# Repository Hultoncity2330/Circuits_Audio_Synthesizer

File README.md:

# Audio Synthesizer — Logic Noise, Breadboard Prototypes & KiCad PCB

**Circuits / CreaTech A4 — November 2026**  
**Team:** Ryan Hulton, Paul Lamour

> An experimental audio synthesizer built from digital logic: we explored oscillator circuits on breadboards, documented their waveforms and sounds, modeled a circuit in Tinkercad, and developed an expanded KiCad schematic and PCB layout.

## 1. Concept and learning objectives

This project explores **logic noise**: producing audible signals from inexpensive digital logic rather than using a conventional synthesizer IC or generating all the audio in software. An inverting Schmitt trigger such as the **74HC14** can form a relaxation oscillator when its output is fed back through a resistance and its input is connected to a capacitor. Changing the resistance changes the charge/discharge timing, and therefore the oscillator frequency.

We experimented with several ways to shape and combine these oscillations. The **LM386** provides an audio amplification stage, while a **74HC595** shift register can drive an eight-LED visual output or support a later stepped control/sequencer design. The **Arduino Uno** shown in the Tinkercad setup is used in the prototyping environment; the KiCad PCB should be understood as a separate hardware design, not proof that an Arduino has been mounted on it.

**Main components represented across the experiments and CAD work:**

- **74HC14** — six inverters with Schmitt-trigger inputs, used for RC oscillator stages.
- **Variable resistors / potentiometers** — frequency adjustment.
- **Capacitors and fixed resistors** — timing, mixing, coupling and supporting circuits.
- **LM386** — audio amplifier for a small speaker.
- **74HC595** — 8-bit shift register and LED outputs.
- **LEDs and resistors** — visual indication, including current limiting in the PCB design.

The following is a **documentation of experiments and design work**; it does not claim that the finalized PCB has already been manufactured or physically tested.

## 2. Experimental process and audiovisual documentation

### 2.1 Breadboard experiments — 9 November 2026

These video files contain **video and embedded audio tracks**, so they are the primary audiovisual records of the breadboard sessions. Click each one to watch and listen on GitHub.

| Recording | Preview / focus | Duration |
| --- | --- | ---: |
| [12:20 — Early circuit test](media/20261109_122047.mp4) | Breadboard wiring, hands-on adjustment and a small speaker | ~7 s |
| [14:56 — Hands-on adjustment](media/20261109_145655.mp4) | Adjusting the breadboard circuit during experimentation | ~17 s |
| [15:11 — Oscilloscope measurement](media/20261109_151122.mp4) | Oscilloscope trace while the circuit is connected | ~37 s |
| [17:20 — Illuminated circuit](media/20261109_172049.mp4) | Breadboard prototype with an illuminated green LED | ~19 s |
| [10 November, 15:21 — Extended prototype](media/20261110_152147.mp4) | Multiple breadboards, Arduino, LED indicators and speaker | ~14 s |

*The descriptions above identify what is visible in the recordings. Precise pitch values, measurements and proof of a soldered assembly have not been independently established from the files.*

### 2.2 Breadboard photographs — 10 November 2026

**Prototype and stripboard preparation**

*Figure 1 — Breadboard setup, connected speaker, and a perforated prototyping board. The photo alone does not establish that the circuit is soldered and functional.*

**Expanded experimental setup**

*Figure 2 — More developed breadboard assembly with additional controls, an Arduino board, a speaker and a perforated board.*

### 2.3 Oscilloscope observations

The oscilloscope was used to inspect the changing electrical signals generated by the breadboard circuits. The screenshots show repeating traces; they should not be treated as calibrated measurements without the matching scale/cursor readings.

| Observation 1 | Observation 2 | Observation 3 |
| :---: | :---: | :---: |
|  |  |  |
| [Full image](media/oscilloscope1.png) | [Full image](media/oscilloscope2.png) | [Full image](media/oscilloscope3.png) |

These observations helped us compare the qualitative shapes of the signals while changing the circuit. For a quantitative account, add the actual oscilloscope time/division, voltage/division, probe attenuation and measured frequencies.

### 2.4 Hand-drawn circuit diagram

*Figure 3 — Working circuit sketch: oscillator/mixing concept, LM386 output stage and planned 74HC595 section. This is an experimental sketch, not the final PCB manufacturing drawing.*

## 3. Tinkercad — virtual breadboard and generated schematic

The experiment was also reconstructed in **Tinkercad Circuits** to show its component placement and wiring before the KiCad design stage.

### Virtual breadboard

[Open full-resolution breadboard image](tinkercad/Tinkercad_breadboard.png)

### Generated electronic schematic

**[View the Tinkercad-generated schematic (PDF)](tinkercad/Tinkercad_schematic.pdf)**

The Tinkercad schematic and physical breadboard view are useful references, but the later KiCad schematic was reconstructed separately, with some implementation changes and design checks. In particular, the real **LM386** pinout must be used for the audio stage rather than treating an incorrectly named amplifier in Tinkercad as electrically interchangeable.

> **File-path check:** These two Tinkercad links use the names seen in the project folder (`Tinkercad_breadboard.png` and `Tinkercad_schematic.pdf`). If the GitHub filenames differ, update these two links to match their exact spelling/capitalization.

## 4. KiCad — expanded schematic and PCB design

The KiCad deliverable is stored in:

**[`kicad/Circuits_Audio_Synth_Kicad_VF/`](kicad/Circuits_Audio_Synth_Kicad_VF/)**

| File | Purpose |
| --- | --- |
| [`Circuits_Audio_Synth_Kicad_VF.kicad_pro`](kicad/Circuits_Audio_Synth_Kicad_VF/Circuits_Audio_Synth_Kicad_VF.kicad_pro) | KiCad project settings |
| [`Circuits_Audio_Synth_Kicad_VF.kicad_sch`](kicad/Circuits_Audio_Synth_Kicad_VF/Circuits_Audio_Synth_Kicad_VF.kicad_sch) | Editable schematic |
| [`Circuits_Audio_Synth_Kicad_VF.kicad_pcb`](kicad/Circuits_Audio_Synth_Kicad_VF/Circuits_Audio_Synth_Kicad_VF.kicad_pcb) | PCB component layout and copper routing |
| [`AudioSynth_Local.pretty/`](kicad/Circuits_Audio_Synth_Kicad_VF/AudioSynth_Local.pretty/) | Project-specific footprints |
| [`Custom.kicad_sym`](kicad/Circuits_Audio_Synth_Kicad_VF/Custom.kicad_sym) | Project-specific schematic symbol library |
| `fp-lib-table` and `sym-lib-table` | Local library registrations |

### Second-version concept / added functionality

Compared with the initial oscillator/mixing experiment, the expanded KiCad design brings together **five adjustable oscillator sections**, **LM386 audio output circuitry**, and an **eight-output 74HC595/LED subsystem** on one PCB design. This provides more possible oscillator combinations and visual output/step-sequencer development than the simple initial oscillator setup.

The eight-LED shift-register section is a **design feature**, not evidence that a complete clocked musical sequencer has been demonstrated on a finished PCB. If the assessment requires an implemented novel behavior, the team should document its actual operation and what was added relative to the **soldered** V1 circuit.

### Layout and verification

- Components are arranged in functional groups: oscillator/timing networks, logic and amplifier ICs, and LED outputs.
- The PCB uses routed front/back copper and a ground copper zone.
- The **last KiCad DRC screenshot provided for the final v8** reported **0 errors**, **0 warnings**, **0 unconnected items**, and **0 schematic/PCB parity discrepancies** (with **5 ignored tests**).
- **These results are CAD rule checks, not a functional test or an assurance of manufacturability.** Actual component-body dimensions and custom footprint geometries must be compared with the parts that will be soldered.

To edit the design, open the `.kicad_pro` file from the directory above and keep the local symbol and footprint libraries in their existing relative positions.

## 5. Soldered prototype

### 5.1 Assembly and soldering progress

After testing our audio synthesizer circuits on breadboards, we began transferring the components onto perforated prototyping boards to build a more permanent physical prototype.

**The soldering process has not yet been completed successfully.** We encountered difficulties assembling the boards and making reliable electrical connections between the components. The photograph below shows the current assembly progress, including the boards for the LED outputs, electronic components and adjustable controls.

*Figure 4 — Work-in-progress assembly on perforated prototyping boards. The soldering and interconnections have not yet been finalized.*

### 5.2 Current status and next steps

Although we tested various oscillator circuits during the breadboard experiments, **we cannot yet confirm that the soldered assembly works**. No functioning soldered prototype has been demonstrated at the time of submission.

Our next steps are to complete the solder joints and wiring, check continuity and possible short circuits, verify the power connections, and test the assembled synthesizer before recording evidence of its operation.

This section documents the unfinished state of the physical prototype rather than presenting it as a completed or verified circuit.

## 6. What we learned and possible next steps

- Simple Schmitt-trigger logic can be used as an experimental sound source with RC feedback.
- Potentiometers change oscillator timing and can create a wide range of audible behavior.
- An oscilloscope is useful for comparing waveforms and investigating unexpected behavior.
- Moving from breadboard experiments to Tinkercad and KiCad requires careful attention to physical pinouts, power rails, resistor values, PCB footprints and track clearances.
- A successful ERC/DRC is necessary for CAD verification, but does **not** guarantee the actual circuit will work after assembly.

Possible future work includes demonstrating a fully clocked 74HC595-driven step pattern, measuring oscillator frequencies quantitatively, testing the soldered hardware and producing a fabrication-verified revision with confirmed component footprints.

## 7. Repository organization

```text
Circuits_Audio_Synthesizer/
├── README.md
├── kicad/
│   └── Circuits_Audio_Synth_Kicad_VF/
│       ├── Circuits_Audio_Synth_Kicad_VF.kicad_pro
│       ├── Circuits_Audio_Synth_Kicad_VF.kicad_sch
│       ├── Circuits_Audio_Synth_Kicad_VF.kicad_pcb
│       ├── AudioSynth_Local.pretty/
│       ├── Custom.kicad_sym
│       ├── sym-lib-table
│       └── fp-lib-table
├── tinkercad/
│   ├── Tinkercad_breadboard.png
│   └── Tinkercad_schematic.pdf
└── media/
    ├── 20261109_122047.mp4
    ├── 20261109_145655.mp4
    ├── 20261109_151122.mp4
    ├── 20261109_172049.mp4
    ├── 20261110_102235.jpg
    ├── 20261110_143109.jpg
    ├── 20261110_152147.mp4
    ├── hand_drawn_circuit.jpg
    ├── oscilloscope1.png
    ├── oscilloscope2.png
    └── oscilloscope3.png
```

---

**Course context:** Logic Noise / Digital Oscillators workshop, CreaTech Circuits, November 2026.  
**Repository:** https://github.com/Hultoncity2330/Circuits_Audio_Synthesizer

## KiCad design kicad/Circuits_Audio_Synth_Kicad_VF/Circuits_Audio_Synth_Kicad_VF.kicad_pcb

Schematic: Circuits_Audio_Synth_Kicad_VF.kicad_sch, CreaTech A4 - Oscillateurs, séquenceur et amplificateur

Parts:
C1, C2, C3, C4, C5, C6: 2.2uF; C_Disc_D5.0mm_W2.5mm_P5.00mm
C7: 2.2uF; CP_Radial_D6.3mm_P2.50mm
C8: 220uF; CP_Radial_D6.3mm_P2.50mm
C11, C12, C13: 100nF; C_Disc_D5.0mm_W2.5mm_P5.00mm
D1, D2, D3, D4, D5, D6, D7, D8, D12: GREEN; LED_D5.0mm
D10: RED; LED_D5.0mm
D11: YELLOW; LED_D5.0mm
D13: BLUE; LED_D5.0mm
J1: ARDUINO_5V_GND; PinHeader_1x02_P2.54mm_Vertical
LS1: Speaker_8ohm; PinHeader_1x02_P2.54mm_Vertical
R1, R2, R3, R4, R5, R11, R12, R13, R14, R15, R20, R21, R22, R23, R24, R25, R26, R27, R30, R31, R32, R33: 1k; R_Axial_DIN0207_L6.3mm_D2.5mm_P7.62mm_Horizontal
R6: 100k; R_Axial_DIN0207_L6.3mm_D2.5mm_P7.62mm_Horizontal
RPOT1, RPOT2, RPOT3, RPOT4, RPOT5: 250k; Potentiometer_Bourns_3296W_Vertical
U2: 74HC595; DIP-16_W7.62mm
U3: 74HC14; DIP-14_W7.62mm
U4: LM386; DIP-8_W7.62mm

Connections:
unnamed: C11.1, C12.1, C13.1, J1.1 (+5V), U2.10 (SRCLR), U2.16 (VCC), U3.14 (VCC), U4.6 (VCC)
unnamed: C1.1, C2.1, C3.1, C4.1, C5.1, C7.2, C11.2, C12.2, C13.2, D1.2 (K), D2.2 (K), D3.2 (K), D4.2 (K), D5.2 (K), D6.2 (K), D7.2 (K), D8.2 (K), D10.2 (K), D11.2 (K), D12.2 (K), D13.2 (K), J1.2 (GND), LS1.2, R6.2, U2.8 (GND), U2.13 (OE), U3.7 (GND), U3.13 (A), U4.2 (IN-), U4.4 (GND)
unnamed: C6.1, R1.2, R2.2, R3.2, R4.2, R5.2
unnamed: C8.2, LS1.1
unnamed: D1.1 (A), R20.2
unnamed: D2.1 (A), R21.2
unnamed: D3.1 (A), R22.2
unnamed: D4.1 (A), R23.2
unnamed: D5.1 (A), R24.2
unnamed: D6.1 (A), R25.2
unnamed: D7.1 (A), R26.2
unnamed: D8.1 (A), R27.2
unnamed: D10.1 (A), R30.2
unnamed: D11.1 (A), R31.2
unnamed: D12.1 (A), R32.2
unnamed: D13.1 (A), R33.2
unnamed: R11.2, RPOT1.1
unnamed: R12.2, RPOT2.1
unnamed: R13.2, RPOT3.1
unnamed: R14.2, RPOT4.1
unnamed: R15.2, RPOT5.1
unnamed: R1.1, R30.1, RPOT1.2 (W), RPOT1.3 (2), U3.2 (Y)
unnamed: R2.1, R31.1, RPOT2.2 (W), RPOT2.3 (2), U2.14 (SER), U3.4 (Y)
unnamed: R3.1, R32.1, RPOT3.2 (W), RPOT3.3 (2), U3.6 (Y)
unnamed: R4.1, RPOT4.2 (W), RPOT4.3 (2), U3.8 (Y)
unnamed: R5.1, R33.1, RPOT5.2 (W), RPOT5.3 (2), U2.11 (SRCLK), U2.12 (RCLK), U3.10 (Y)
unnamed: R20.1, U2.15 (Q0)
unnamed: R21.1, U2.1 (Q1)
unnamed: R22.1, U2.2 (Q2)
unnamed: R23.1, U2.3 (Q3)
unnamed: R24.1, U2.4 (Q4)
unnamed: R25.1, U2.5 (Q5)
unnamed: R26.1, U2.6 (Q6)
unnamed: R27.1, U2.7 (Q7)
unnamed: C1.2, R11.1, U3.1 (A)
unnamed: C2.2, R12.1, U3.3 (A)
unnamed: C3.2, R13.1, U3.5 (A)
unnamed: C4.2, R14.1, U3.9 (A)
unnamed: C5.2, R15.1, U3.11 (A)
unnamed: C7.1, U4.7 (BYPASS)
unnamed: C6.2, R6.1, U4.3 (IN+)
unnamed: C8.1, U4.5 (OUT)

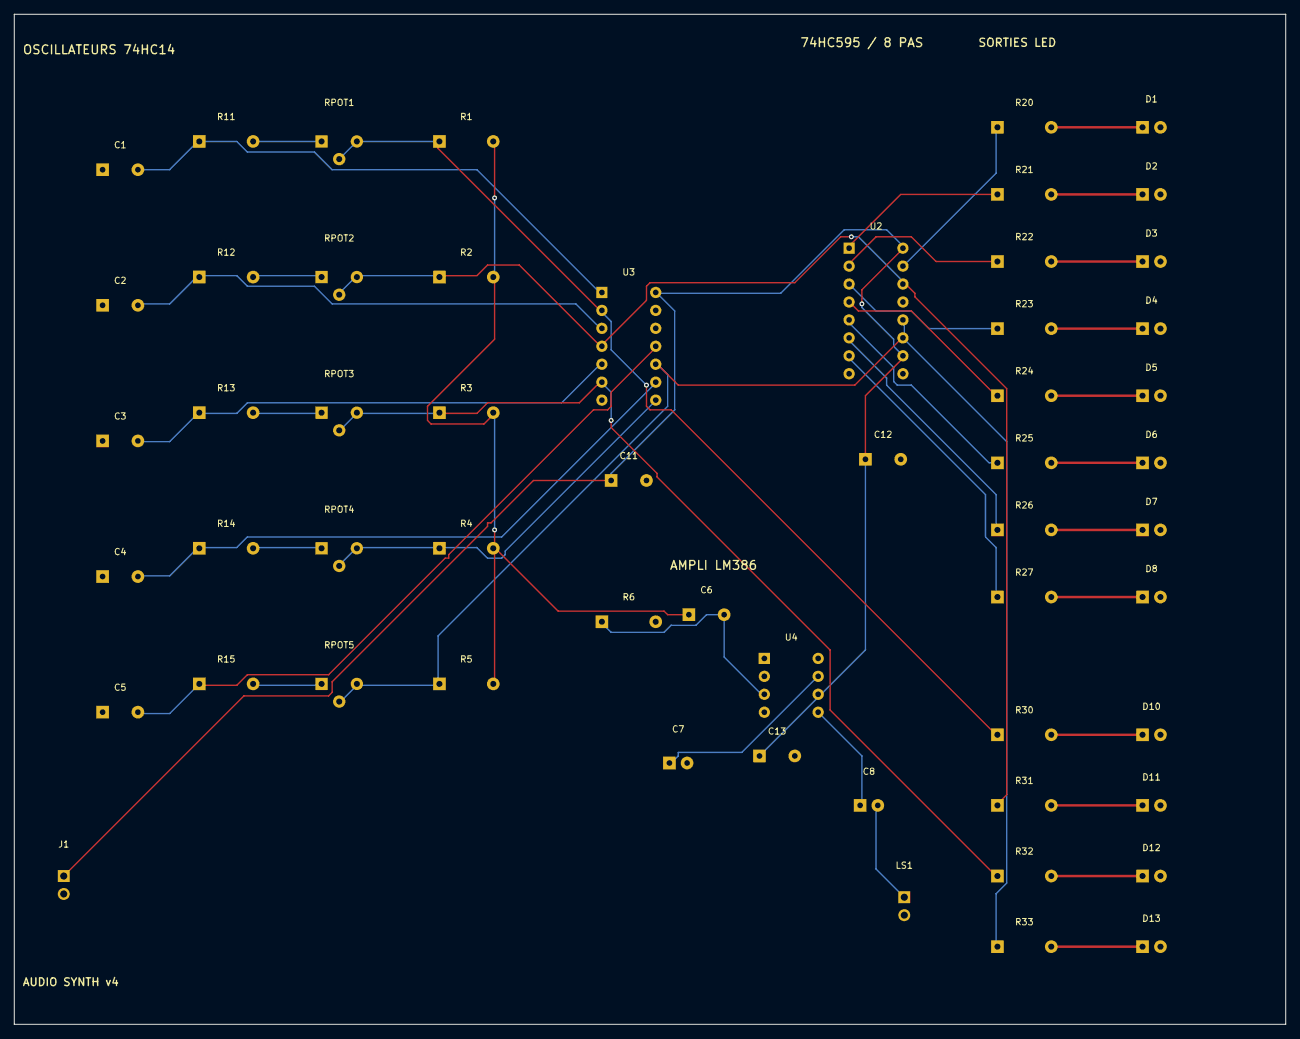
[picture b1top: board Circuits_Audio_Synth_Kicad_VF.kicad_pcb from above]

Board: 2 copper layers, 180.0 x 143.0 mm, 56 parts (0 on the bottom side), 42 nets.
